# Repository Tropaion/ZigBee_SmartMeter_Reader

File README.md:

# ZigBee_SmartMeter_Reader
This is an open-source ZigBee device based on the new ESP32-C6 to collect data from smartmeters using the DLMS/COSEM protocol.

Ever since I got the smartmeter "Sagemcom T-210D" with the P1 user interface, I wanted to integrate it into my ZigBee network.
Since I didn't find any existing solution, I decided to develop my own.

If someone is interested in buying an assembled PCB, pm me.
Currently I have one board with external antenna available.

THE PROJECT IS STILL WIP.

# Hardware
View the latest [PCB Interactive BOM](https://htmlpreview.github.io/?https://github.com/Tropaion/ZigBee_SmartMeter_Reader/blob/main/hardware/onboard_antenna/bom/ibom.html).

You can also view the latest [Schematic](https://kicanvas.org/?github=https%3A%2F%2Fgithub.com%2FTropaion%2FZigBee_SmartMeter_Reader%2Fblob%2Fmain%2Fhardware%2Fexternal_antenna%2FZBSmartMeter.kicad_sch) or [Layout](https://kicanvas.org/?github=https%3A%2F%2Fgithub.com%2FTropaion%2FZigBee_SmartMeter_Reader%2Fblob%2Fmain%2Fhardware%2Fexternal_antenna%2FZBSmartMeter.kicad_pcb).

The same hardware could also be used with WLAN and ESPHome.

For this project, I used the [ESP32-C6-MINI-1U](https://www.espressif.com/sites/default/files/documentation/esp32-c6-mini-1_mini-1u_datasheet_en.pdf).
I chose the version with an external antenna, since, in most cases, the devices will be mounted in an isolated meter box. And, since many of them are made of metal (Faraday cage), like in my case, 
I opted for an external antenna to mount on the outside of the meter box.

To provide easy flashing and debugging the USB-C-Socket is connected to the ESP internal USB-JTAG-Converter.
In the case that the converter is not working, the UART0 programming interface is connected to J2 and J3, which will not be assembled.

For production use in the meter box, only the 5V supply terminal (J5) which in my case will be connected to a 5V DIN Power Supply and RJ12 (J1) cable going to the smartmeter is needed.

Since most smartmeters send encrypted data, you probably need to request an decryption key from your provider.
This key has to be configured in the software. The current plan for this is to provide a simple configuration terminal which is accessible via the USB-C-Socket.

# Software
The software will be separated into three core components/libraries.
Each will be individually tested and then combined.
- [x] human_interface - handles button input and led (working)
- [x] zigbee - handles zigbee basic functions
- [x] zigbee_electricity_meter - handles everything zigbee and electricity meter related (cluster)
- [ ] smartmeter - read data via uart, parse layers and decrypt data

Possible additional functionalities:
- [ ] zigbee_ota - updating firmware via zigbee
- [ ] configuration_console - usb console to configure device (decryption key)

OR
- [ ] zigbee custom configuration cluster - cluster configure device (decryption key)

## Structure of SmartMeter data
How the data is handled is a bit complicated and consists of three layers:
- MBUS-Layer
- DLMS-Layer
- OBIS-Layer

Each layer will be handled by a parser.

See the diagram to understand the structure and how the parser handles the data:

## Sources
 * [esphome-dlms-meter](https://github.com/DomiStyle/esphome-dlms-meter)
 * [SmartMeter P1 Interface](https://www.netz-noe.at/Download-(1)/Smart-Meter/218_9_SmartMeter_Kundenschnittstelle_lektoriert_14.aspx)
 * [M-Bus Specification, Page 22+](https://m-bus.com/assets/downloads/MBDOC48.PDF)
 * [ZigBee Home Automation Profile](https://community.nxp.com/pwmxy87654/attachments/pwmxy87654/wireless-connectivity/698/1/075367r03ZB_AFG-Home_Automation_Profile_for_Public_Download.pdf)
 * [ZigBee Cluster Library Specification](https://zigbeealliance.org/wp-content/uploads/2019/12/07-5123-06-zigbee-cluster-library-specification.pdf)

# Enclosue
The first version of the enclosure is released and now in printing.

# Attribution
Thanks to EspressIf for sponsoring two samples of [ESP32-C6-MINI-1U](https://www.espressif.com/sites/default/files/documentation/esp32-mini-1_datasheet_en.pdf).

Thanks to [PCBWay](https://www.pcbway.com/) for sponsoring the production of the PCB and Stencil for v0.2. It was my first time using their service and they have nice customer service and great build quality. The image in the hardware section shows the result of v0.2.

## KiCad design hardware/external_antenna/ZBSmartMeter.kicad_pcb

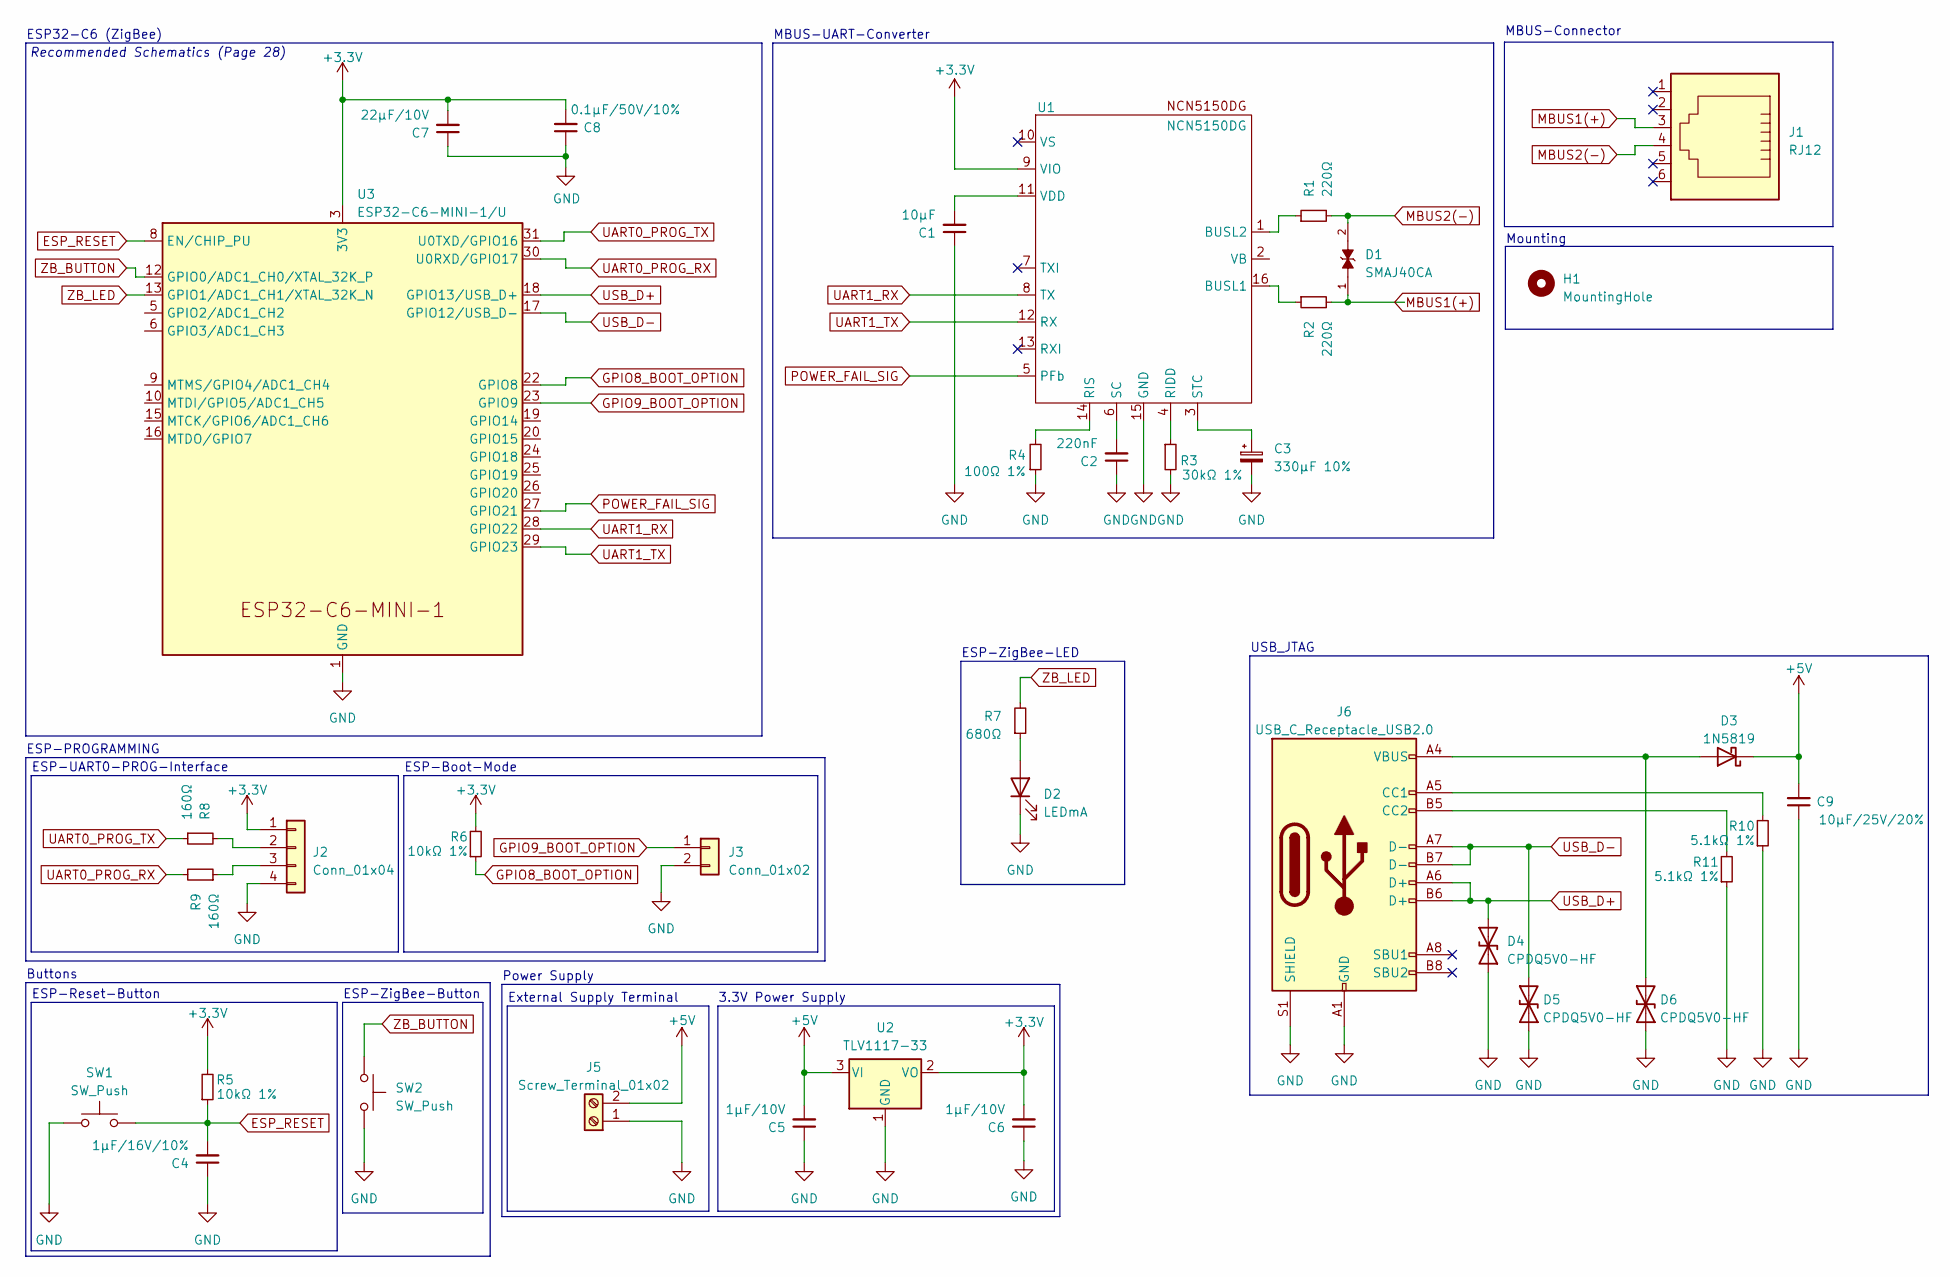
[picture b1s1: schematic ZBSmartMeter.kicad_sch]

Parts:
C1: 10µF; C_0603_1608Metric
C2: 220nF; C_0603_1608Metric
C3: 330µF 10%; CP_Elec_8x10.5
C4: 1µF/16V/10%; C_0603_1608Metric
C5, C6: 1µF/10V; C_0603_1608Metric
C7: 22µF/10V; C_0805_2012Metric
C8: 0.1µF/50V/10%; C_0603_1608Metric
C9: 10µF/25V/20%; C_0603_1608Metric
D1: SMAJ40CA; DIOM4325X250N; PARTREV S2102; Mouser 576-SMAJ40CA
D2: LEDmA; LED_0603_1608Metric
D3: 1N5819; D_SOD-123; Mouser 621-1N5819HW-F
D4, D5, D6: CPDQ5V0-HF; D_SOD-923; Mouser 750-CPDQ5V0-HF
H1: MountingHole; MountingHole_2.2mm_M2
J1: RJ12; RJ12_Amphenol_54601; Mouser 649-54601-906WPLF
J2: Conn_01x04; PinHeader_1x04_P2.54mm_Vertical
J3: Conn_01x02; PinHeader_1x02_P2.54mm_Vertical
J5: Screw_Terminal_01x02; PhoenixContact_MSTBA_2,5_2-G_1x02_P5.00mm_Horizontal; Mouser 651-1923759 and 651-1942154
J6: USB_C_Receptacle_USB2.0; USB_C_Receptacle_GCT_USB4105-xx-A_16P_TopMnt_Horizontal; Mouser 640-USB4105-GF-A
R1, R2: 220Ω; R_0603_1608Metric
R3: 30kΩ 1%; R_0603_1608Metric
R4: 100Ω 1%; R_0603_1608Metric
R5, R6: 10kΩ 1%; R_0603_1608Metric
R7: 680Ω; R_0603_1608Metric
R8, R9: 160Ω; R_0603_1608Metric
R10, R11: 5.1kΩ 1%; R_0603_1608Metric
SW1, SW2: SW_Push; SW_SPST_TL3305A; Mouser 612-TL3305AF160QG
U1: NCN5150DG; SOIC-16_3.9x9.9mm_P1.27mm; Mouser 863-NCN5150DR2G
U2: TLV1117-33; SOT-223-3_TabPin2; Mouser 595-TLV1117LV33DCYT
U3: ESP32-C6-MINI-1/U; ESP32-C6-MINI-1U

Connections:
+3.3V: C6.2, C7.2, C8.2, J2.1, R5.2, R6.2, U1.9 (VIO), U2.2 (VO), U3.3 (3V3)
+5V: C5.2, C9.2, D3.1 (K), J5.2, U2.3 (VI)
ESP_RESET: C4.2, R5.1, SW1.2, U3.8 (EN/CHIP_PU)
GND: C1.1, C2.1, C3.2, C4.1, C5.1, C6.1, C7.1, C8.1, C9.1, D2.1 (K), D4.1 (A1), D5.1 (A1), D6.1 (A1), J2.4, J3.2, J5.1, J6.A1 (GND), J6.A12 (GND), J6.B1 (GND), J6.B12 (GND), J6.S1 (SHIELD), R3.2, R4.1, R10.1, R11.1, SW1.1, SW2.2, U1.15 (GND), U2.1 (GND), U3.1 (GND), U3.2 (GND), U3.11 (GND), U3.14 (GND), U3.36 (GND), U3.37 (GND), U3.38 (GND), U3.39 (GND), U3.40 (GND), U3.41 (GND), U3.42 (GND), U3.43 (GND), U3.44 (GND), U3.45 (GND), U3.46 (GND), U3.47 (GND), U3.48 (GND), U3.49 (GND), U3.50 (GND), U3.51 (GND), U3.52 (GND), U3.53 (GND)
GPIO8_BOOT_OPTION: R6.1, U3.22 (GPIO8)
GPIO9_BOOT_OPTION: J3.1, U3.23 (GPIO9)
MBUS1(+): D1.1, J1.3, R2.2
MBUS2(-): D1.2, J1.4, R1.2
unnamed: D2.2 (A), R7.1
unnamed: D3.2 (A), D6.2 (A2), J6.A4 (VBUS), J6.A9 (VBUS), J6.B4 (VBUS), J6.B9 (VBUS)
unnamed: J2.2, R8.2
unnamed: J2.3, R9.1
unnamed: J6.A5 (CC1), R10.2
unnamed: J6.B5 (CC2), R11.2
unnamed: R2.1, U1.16 (BUSL1)
unnamed: R1.1, U1.1 (BUSL2)
unnamed: R3.1, U1.4 (RIDD)
unnamed: R4.2, U1.14 (RIS)
unnamed: C2.2, U1.6 (SC)
unnamed: C3.1, U1.3 (STC)
unnamed: C1.2, U1.11 (VDD)
POWER_FAIL_SIG: U1.5 (PFb), U3.27 (GPIO21)
UART0_PROG_RX: R9.2, U3.30 (U0RXD/GPIO17)
UART0_PROG_TX: R8.1, U3.31 (U0TXD/GPIO16)
UART1_RX: U1.8 (TX), U3.28 (GPIO22)
UART1_TX: U1.12 (RX), U3.29 (GPIO23)
USB_D+: D4.2 (A2), J6.A6 (D+), J6.B6 (D+), U3.18 (GPIO13/USB_D+)
USB_D-: D5.2 (A2), J6.A7 (D-), J6.B7 (D-), U3.17 (GPIO12/USB_D-)
ZB_BUTTON: SW2.1, U3.12 (GPIO0/ADC1_CH0/XTAL_32K_P)
ZB_LED: R7.2, U3.13 (GPIO1/ADC1_CH1/XTAL_32K_N)

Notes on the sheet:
Mounting
ESP-ZigBee-Button
MBUS-Connector
3.3V Power Supply
ESP-UART0-PROG-Interface
External Supply Terminal
ESP-PROGRAMMING
USB_JTAG
ESP-ZigBee-LED
Buttons
ESP-Reset-Button
ESP-Boot-Mode
MBUS-UART-Converter
ESP32-C6 (ZigBee)
Recommended Schematics (Page 28)
Power Supply

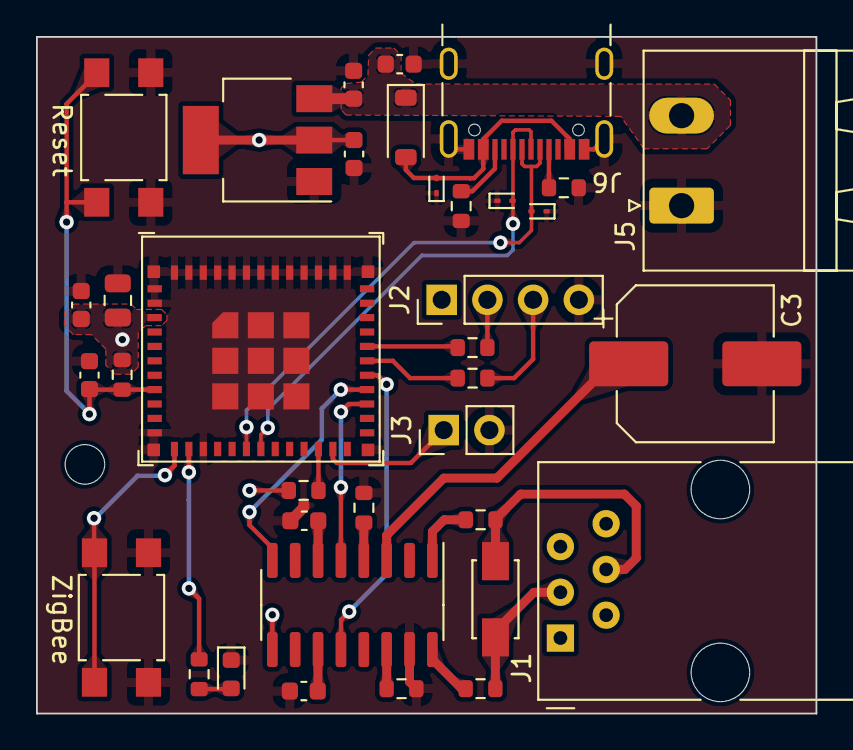
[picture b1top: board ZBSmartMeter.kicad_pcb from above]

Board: 2 copper layers, 43.3 x 37.6 mm, 37 parts (0 on the bottom side), 30 nets.

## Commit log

2023-07-10 added hardware
2023-07-10 update hardware + documentation
2023-07-10 added images
2023-07-10 Fix gerber
2023-07-18 fixed diode error, improved layout
2023-07-18 Update gerber
2023-07-26 software
2023-07-27 Add enclosure files
2023-07-28 LED to bright, change resistor value
2023-07-28 Add human interface code, edit readme
2023-08-02 dlms in progress
2023-08-02 basic zigbee implementation, merge "human_interface" into zigbee
2023-08-04 small changes
2023-08-05 stuff
2023-08-05 MBUS-Layer-Handling added
2023-08-06 Update doku
2023-08-06 Fix doku
2023-08-06 Update image
2023-08-06 Fix image
2023-08-06 Working dlms parser
2023-08-07 uart stuff
2023-08-15 Initial hardware design for ESP32-C6-WROOM-1
2023-08-15 Finalize UART event handling
2023-08-15 Improve UART Error handling
2023-08-15 Fix uart task stack size
2023-08-16 Fix UART Loop
2023-08-16 UART Event now working
2023-08-16 Minor fixes
2023-08-16 Cleanup + improved documentation
2023-08-18 ZigBee Stuff
2023-08-23 Add ZigBee Cluster and update function for electricity meter
2023-08-23 Add DATA_MEASUREMENT_INTERVAL
2023-08-23 useless stuff
2023-08-23 zigbee testing
2023-08-28 obis stuff
2023-08-29 Restructuring library
2023-11-29 editing enclosure
2024-02-03 new enclosure
2024-02-03 edit enclosure
2024-02-06 improved enclosure
2024-02-11 enclosure_final
2024-03-05 Bump to KiCad8
